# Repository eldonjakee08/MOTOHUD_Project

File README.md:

# MotoHUD Project
A proof of concept project that aims to integrate a heads-up display (HUD) into a motorcycle helmet, projecting real-time ECU sensor data such as speed, RPM, and engine load directly into the rider’s field of view.

This project aims to enhance riders situational awareness and safety by delivering vehicle metrics without requiring the rider to look away from the road.

# System Architecture & Overview

<br>**TRANSMITTER**
1. STM32WB5MMG MCU wakes up every 100ms to poll the motorcycle CAN bus for ECU sensor data.(e.g. Speed, RPM, Engine Load, etc.) 
2. Transmitter sends the ECU sensor data via BLE.
3. MCU goes into deep sleep state to conserve power. 

<br>**RECEIVER**
1. STM32WB5MMG MCU wakes up from deep sleep upon reception of sensor data from transmitter
2. MCU Parses the received data and displays into OLED screen.
3. Beamsplitter glass reflects the projection from OLED screen into the riders field of view
4. MCU returns into deep sleep state to conserve power.

# Project Milestones & Progress
1. Designed and fabricated a custom development board for STM32WB5MMG MCU.
2. Designed and fabricated custom module for LM3671 to power the receiver.
3. Designed the initial hardware for both Receiver and Transmitter.
4. Developed custom driver for SSD1315 OLED driver.
5. On-going development of custom driver for MCP2515 CAN controller

# Pending Tasks
1. Develop application firmware for both receiver and transmitter.
2. Fabricate the hardware for both receiver and transmitter.
3. Design and fabricate a receiver enclosure for optimal mounting into the helmet.
4. Design and fabricate an enclosure for the transmitter.

 # Future Improvements & Optimizations
 1. Optimize I2C and SPI data transmission using Direct Memory Access (DMA) to achieve higher throughput and lower power consumption.
 2. Design a load sharing protection circuit for the receiver’s battery to support simultaneous operation and charging.
 3. Music streaming feature via Bluetooth Low Energy (BLE).
 4. END VISION: Seamlessly stream live ECU sensor data into the helmets visor, delivering a real-time Augmented Reality (AR) experience.

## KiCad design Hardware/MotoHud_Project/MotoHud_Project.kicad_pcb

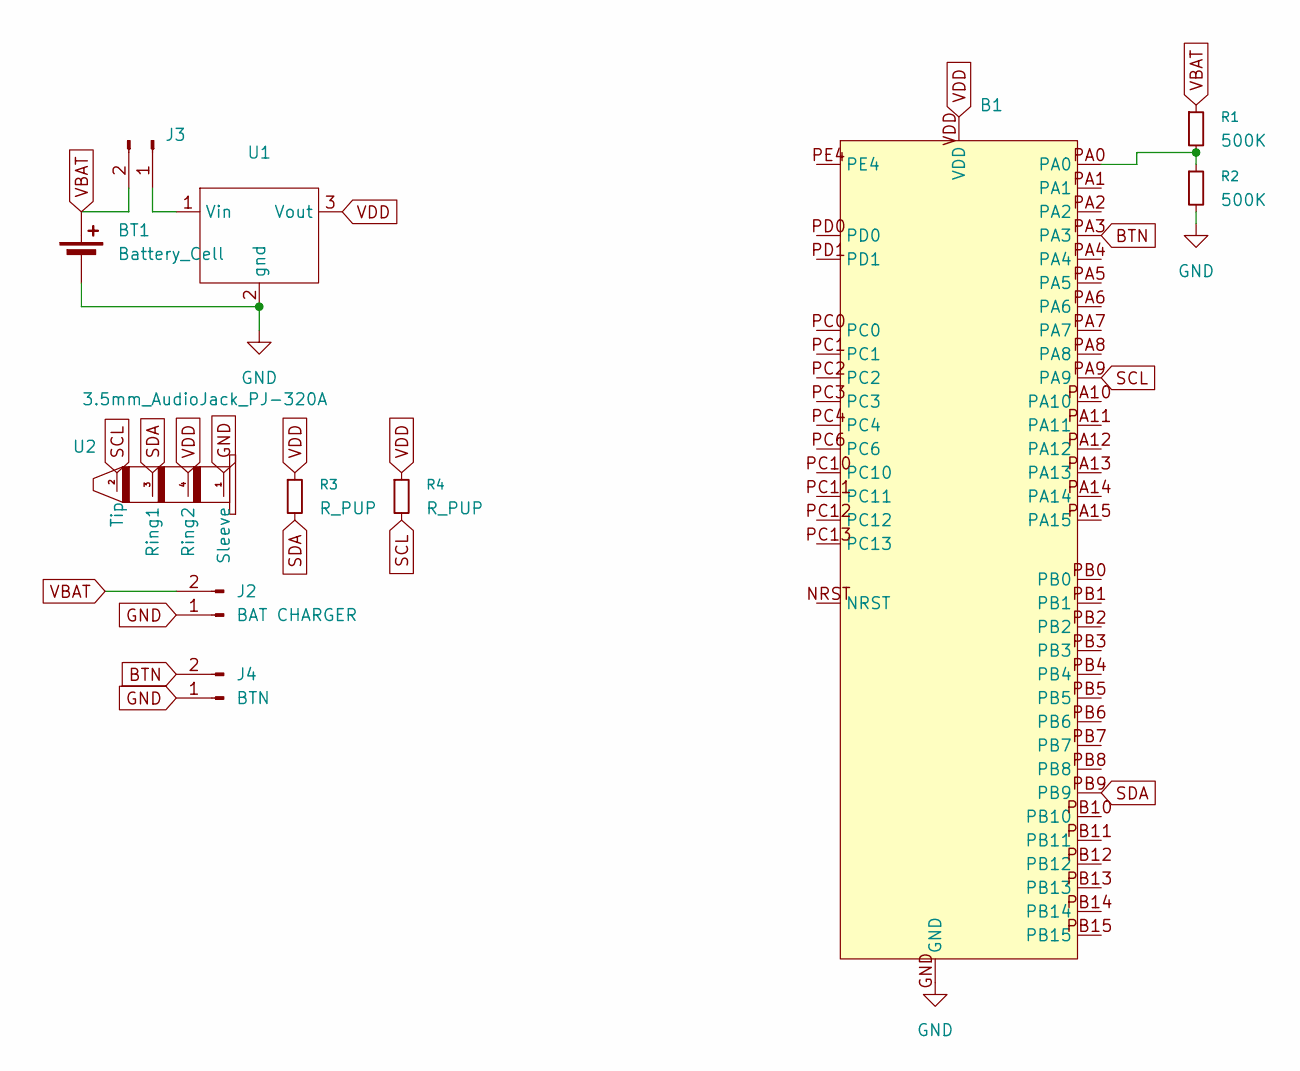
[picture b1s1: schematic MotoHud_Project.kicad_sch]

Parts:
B1: STM32WB5MMG_CUSTOM_DEVBOARD
BT1: Battery_Cell; PinHeader_1x02_P2.54mm_Vertical
J2: BAT CHARGER; PinHeader_1x02_P2.54mm_Vertical
J3: Conn_01x02_Pin; PinHeader_1x02_P2.54mm_Vertical
J4: BTN; PinHeader_1x02_P2.54mm_Vertical
R1, R2: 500K; R_0603_1608Metric_Pad0.98x0.95mm_HandSolder
R3, R4: R_PUP; R_Axial_DIN0207_L6.3mm_D2.5mm_P10.16mm_Horizontal
U1: LM3671_MODULE
U2: 3.5mm_AudioJack_PJ-320A; 3.5mm_AudioJack_PJ-320A_NoGuide

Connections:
BTN: B1.PA3, J4.2
GND: B1.GND, BT1.2 (-), J2.1, J4.1, R2.2, U1.2 (gnd), U2.1 (Sleeve)
unnamed: B1.PA0, R1.2, R2.1
unnamed: J3.1, U1.1 (Vin)
SCL: B1.PA9, R4.2, U2.2 (Tip)
SDA: B1.PB9, R3.2, U2.3 (Ring1)
VBAT: BT1.1 (+), J2.2, J3.2, R1.1
VDD: B1.VDD, R3.1, R4.1, U1.3 (Vout), U2.4 (Ring2)

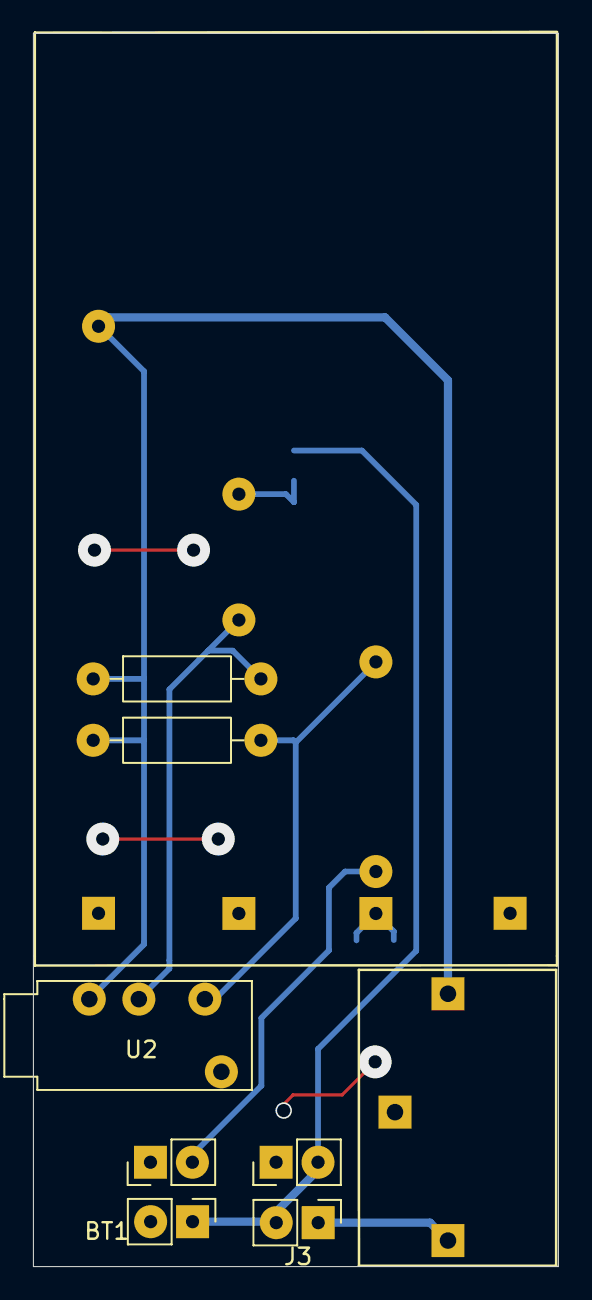
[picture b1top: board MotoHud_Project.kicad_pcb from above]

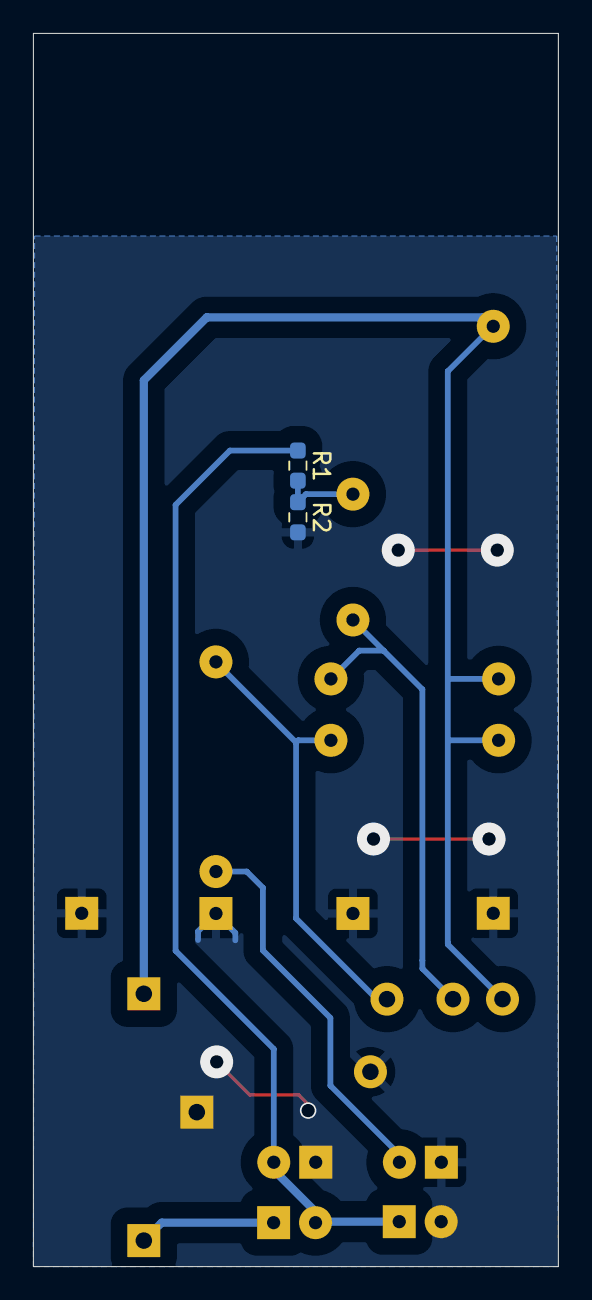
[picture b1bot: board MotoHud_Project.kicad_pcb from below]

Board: 2 copper layers, 31.8 x 74.7 mm, 11 parts (2 on the bottom side), 8 nets.

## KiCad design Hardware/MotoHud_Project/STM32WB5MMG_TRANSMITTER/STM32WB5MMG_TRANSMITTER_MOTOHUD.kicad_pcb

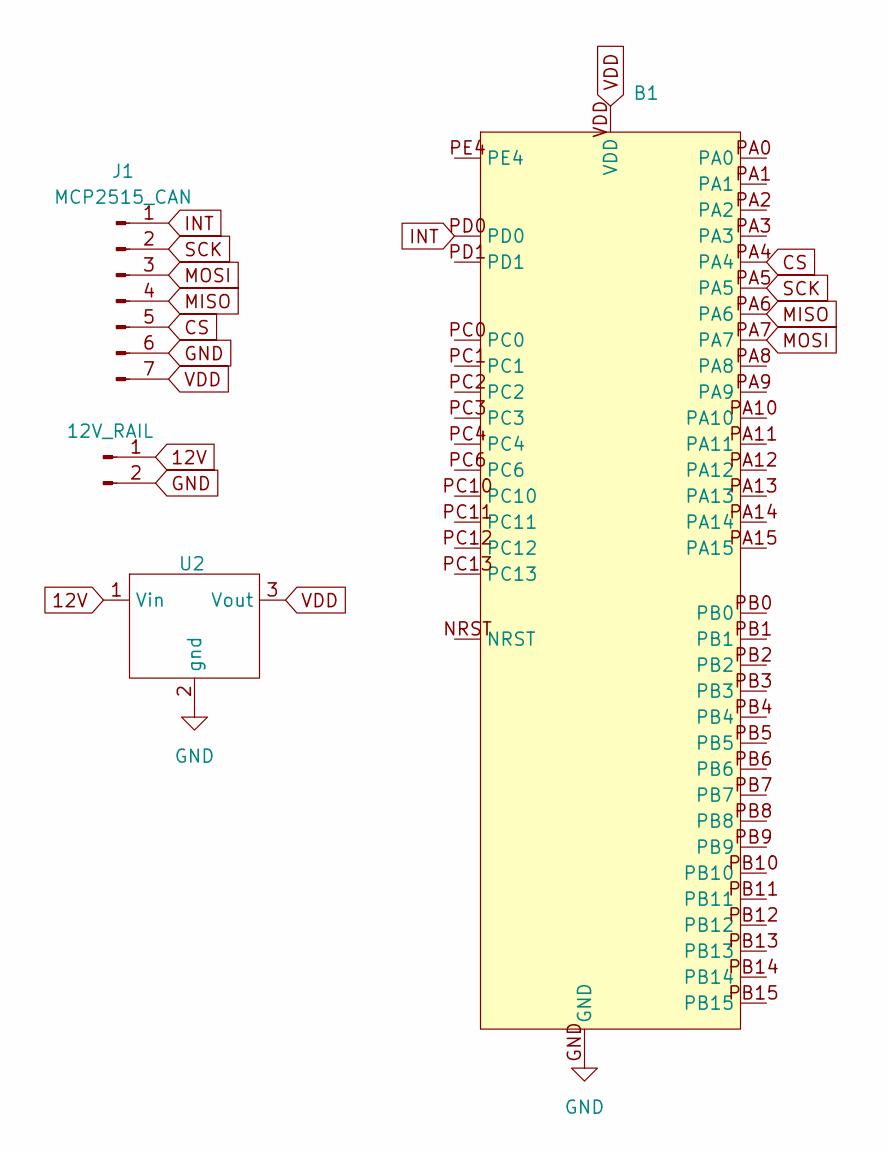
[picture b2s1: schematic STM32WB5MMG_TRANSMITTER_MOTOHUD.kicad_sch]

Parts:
B1: STM32WB5MMG_CUSTOM_DEVBOARD
J1: MCP2515_CAN; MCP2515_MODULE
J3: 12V_RAIL; PinHeader_1x02_P2.54mm_Vertical
U2: MP1584EN_DCtoDC_REGULATOR

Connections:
12V: J3.1, U2.1 (Vin)
CS: B1.PA4, J1.5
GND: B1.GND, J1.6, J3.2, U2.2 (gnd)
INT: B1.PD0, J1.1
MISO: B1.PA6, J1.4
MOSI: B1.PA7, J1.3
SCK: B1.PA5, J1.2
VDD: B1.VDD, J1.7, U2.3 (Vout)

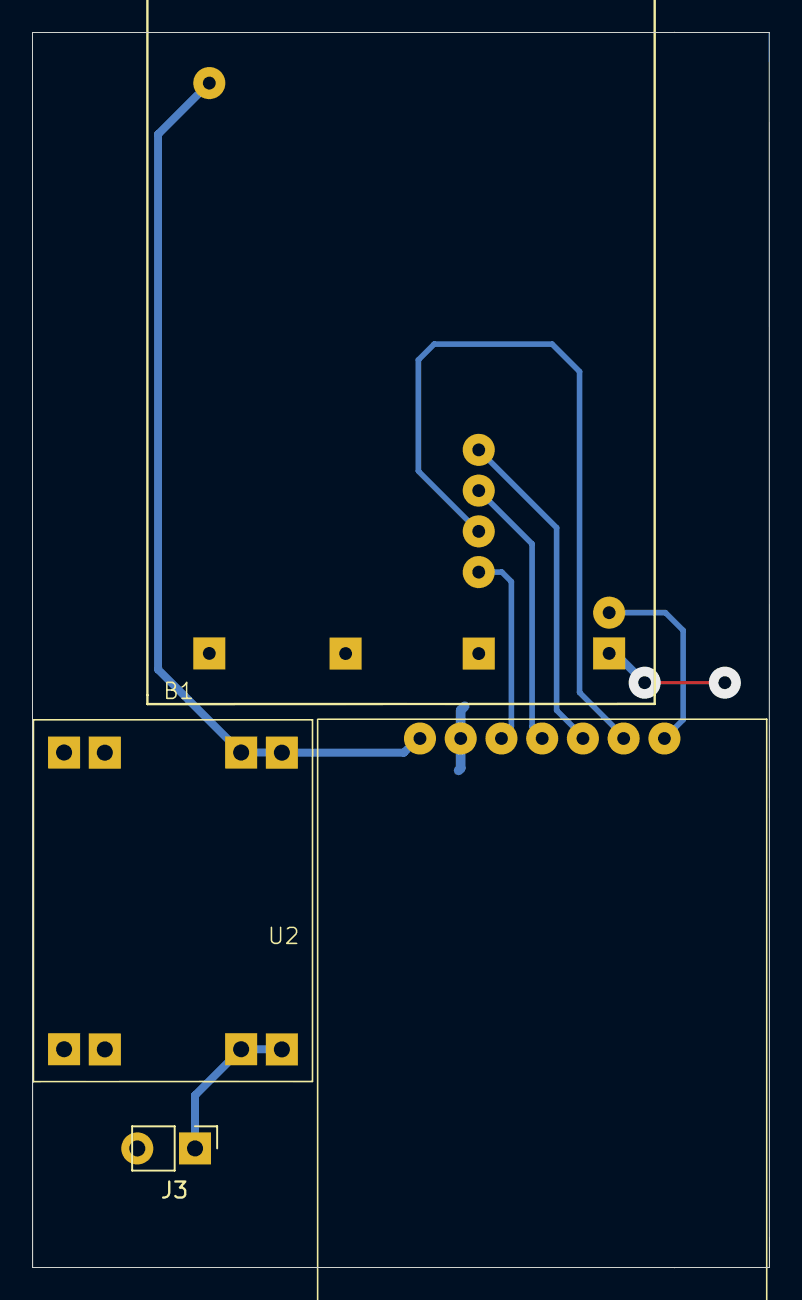
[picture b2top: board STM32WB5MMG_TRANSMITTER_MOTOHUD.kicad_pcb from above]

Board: 2 copper layers, 46.0 x 77.0 mm, 4 parts (0 on the bottom side), 8 nets.

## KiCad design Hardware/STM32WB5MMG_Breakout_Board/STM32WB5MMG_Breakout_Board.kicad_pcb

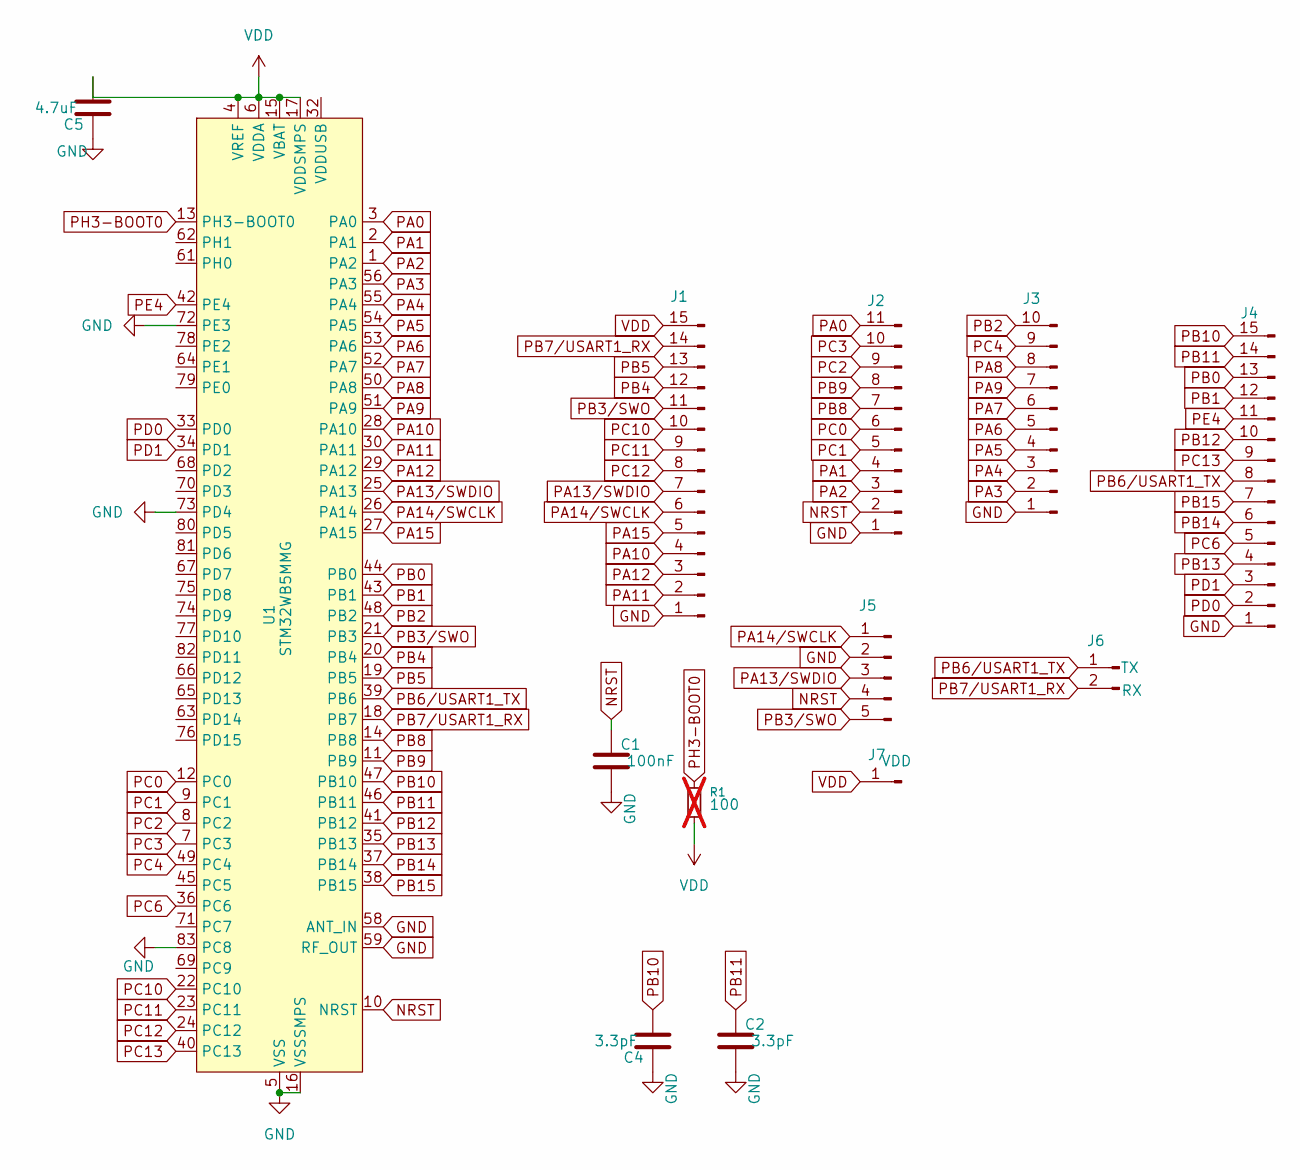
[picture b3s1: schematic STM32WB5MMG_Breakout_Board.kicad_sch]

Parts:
C1: 100nF; C_0603_1608Metric
C2, C4: 3.3pF; C_0201_0603Metric
C5: 4.7uF; C_0603_1608Metric
J1, J4: PinHeader_1x15_P2.54mm_Vertical
J2: Conn_01x11_Pin; PinHeader_1x11_P2.54mm_Vertical
J3: PinHeader_1x10_P2.54mm_Vertical
J5: PinHeader_1x05_P2.54mm_Vertical
J6: PinHeader_1x02_P2.54mm_Vertical
J7: VDD; PinHeader_1x01_P2.54mm_Vertical
R1: 100; R_0201_0603Metric; not fitted
U1: STM32WB5MMG; ST-SiP-LGA-86-11x7.3mm

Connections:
GND: C1.2, C2.2, C4.1, C5.1, J1.1, J2.1, J3.1, J4.1, J5.2, U1.5 (VSS), U1.16 (VSSSMPS), U1.31 (VSS), U1.57 (VSS), U1.58 (ANT_IN), U1.59 (RF_OUT), U1.60 (VSS), U1.72 (PE3), U1.73 (PD4), U1.83 (PC8), U1.84 (VSS), U1.86 (VSS)
NRST: C1.1, J2.2, J5.4, U1.10 (NRST)
PA0: J2.11, U1.3 (PA0)
PA1: J2.4, U1.2 (PA1)
PA2: J2.3, U1.1 (PA2)
PA3: J3.2, U1.56 (PA3)
PA4: J3.3, U1.55 (PA4)
PA5: J3.4, U1.54 (PA5)
PA6: J3.5, U1.53 (PA6)
PA7: J3.6, U1.52 (PA7)
PA8: J3.8, U1.50 (PA8)
PA9: J3.7, U1.51 (PA9)
PA10: J1.4, U1.28 (PA10)
PA11: J1.2, U1.30 (PA11)
PA12: J1.3, U1.29 (PA12)
PA13/SWDIO: J1.7, J5.3, U1.25 (PA13)
PA14/SWCLK: J1.6, J5.1, U1.26 (PA14)
PA15: J1.5, U1.27 (PA15)
PB0: J4.13, U1.44 (PB0)
PB1: J4.12, U1.43 (PB1)
PB2: J3.10, U1.48 (PB2)
PB3/SWO: J1.11, J5.5, U1.21 (PB3)
PB4: J1.12, U1.20 (PB4)
PB5: J1.13, U1.19 (PB5)
PB6/USART1_TX: J4.8, J6.1, U1.39 (PB6)
PB7/USART1_RX: J1.14, J6.2, U1.18 (PB7)
PB8: J2.7, U1.14 (PB8)
PB9: J2.8, U1.11 (PB9)
PB10: C4.2, J4.15, U1.47 (PB10)
PB11: C2.1, J4.14, U1.46 (PB11)
PB12: J4.10, U1.41 (PB12)
PB13: J4.4, U1.35 (PB13)
PB14: J4.6, U1.37 (PB14)
PB15: J4.7, U1.38 (PB15)
PC0: J2.6, U1.12 (PC0)
PC1: J2.5, U1.9 (PC1)
PC2: J2.9, U1.8 (PC2)
PC3: J2.10, U1.7 (PC3)
PC4: J3.9, U1.49 (PC4)
PC6: J4.5, U1.36 (PC6)
PC10: J1.10, U1.22 (PC10)
PC11: J1.9, U1.23 (PC11)
PC12: J1.8, U1.24 (PC12)
PC13: J4.9, U1.40 (PC13)
PD0: J4.2, U1.33 (PD0)
PD1: J4.3, U1.34 (PD1)
PE4: J4.11, U1.42 (PE4)
PH3-BOOT0: R1.1, U1.13 (PH3-BOOT0)
VDD: C5.2, J1.15, J7.1, R1.2, U1.4 (VREF), U1.6 (VDDA), U1.15 (VBAT), U1.17 (VDDSMPS)

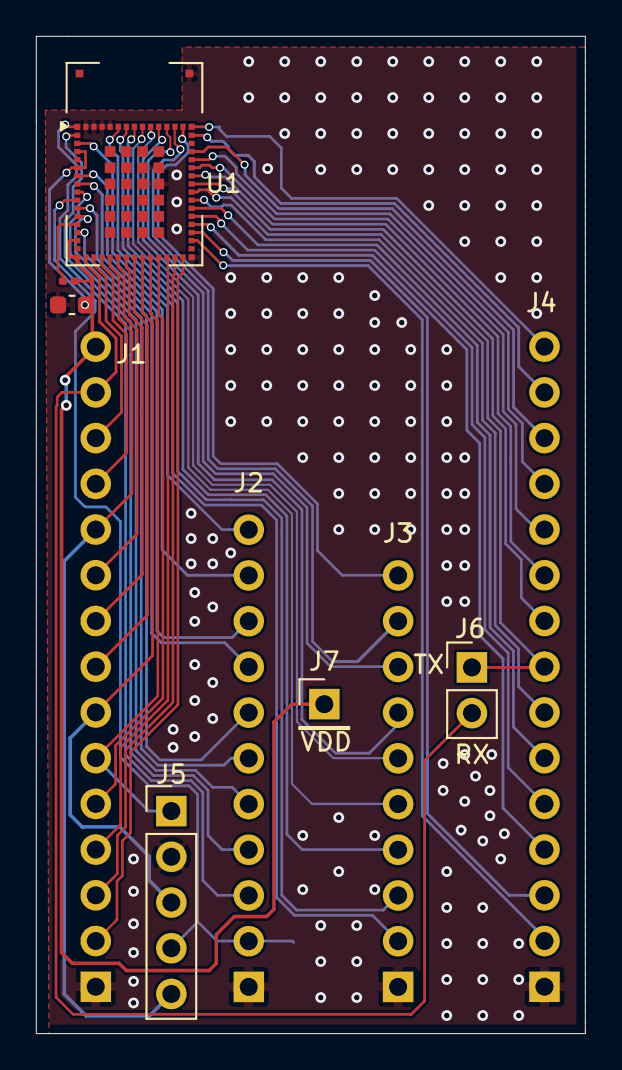
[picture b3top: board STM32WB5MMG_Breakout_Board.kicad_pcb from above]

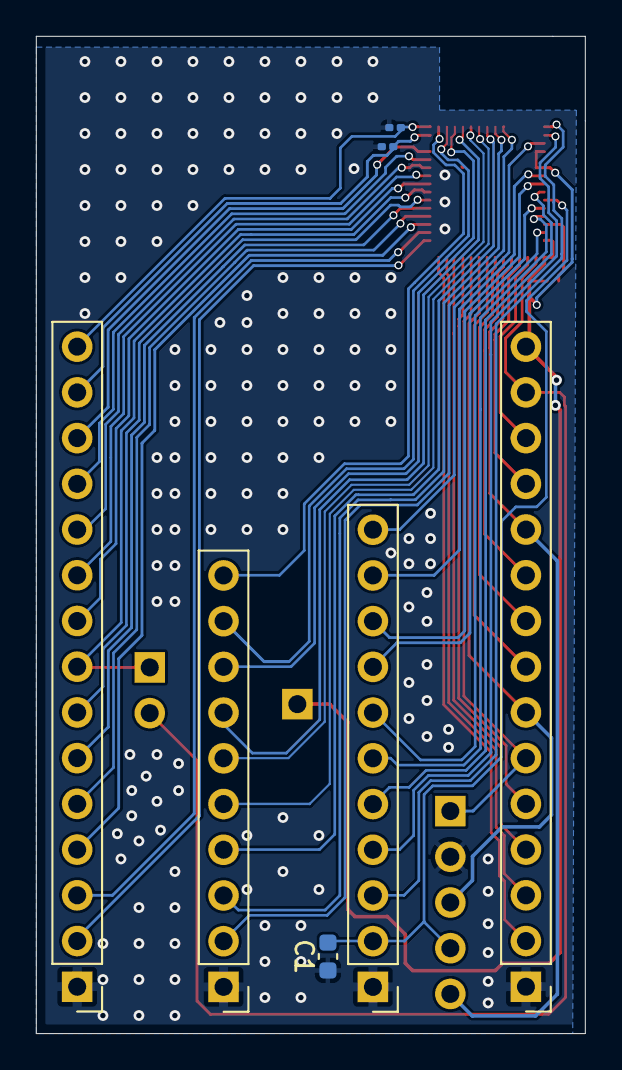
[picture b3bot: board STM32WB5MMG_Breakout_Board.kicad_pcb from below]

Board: 2 copper layers, 30.5 x 55.4 mm, 13 parts (7 on the bottom side), 49 nets.

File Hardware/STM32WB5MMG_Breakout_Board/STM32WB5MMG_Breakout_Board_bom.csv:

Comment,Designator,Footprint
100nF,C1,Capacitor_SMD:C_0603_1608Metric
3.3pF,"C2,C4",Capacitor_SMD:C_0201_0603Metric
4.7uF,C5,Capacitor_SMD:C_0603_1608Metric
Conn_01x15_Pin,"J1,J4",Connector_PinHeader_2.54mm:PinHeader_1x15_P2.54mm_Vertical
Conn_01x11_Pin,J2,Connector_PinHeader_2.54mm:PinHeader_1x11_P2.54mm_Vertical
Conn_01x10_Pin,J3,Connector_PinHeader_2.54mm:PinHeader_1x10_P2.54mm_Vertical
Conn_01x05_Pin,J5,Connector_PinHeader_2.54mm:PinHeader_1x05_P2.54mm_Vertical
Conn_01x2_Pin,J6,Connector_PinHeader_2.54mm:PinHeader_1x02_P2.54mm_Vertical
Conn_01x1_Pin,J7,Connector_PinHeader_2.54mm:PinHeader_1x01_P2.54mm_Vertical
100 Ohms,R1,Resistor_SMD:R_0201_0603Metric
STM32WB5MMG,U1,RF_Module:ST-SiP-LGA-86-11x7.3mm

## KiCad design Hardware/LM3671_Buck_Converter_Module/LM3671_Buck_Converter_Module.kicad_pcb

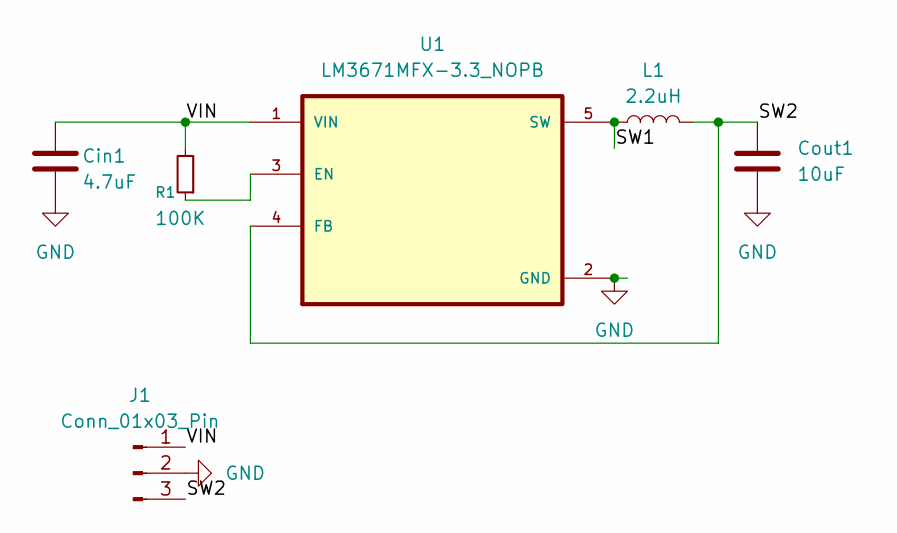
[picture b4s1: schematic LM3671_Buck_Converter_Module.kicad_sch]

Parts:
Cin1: 4.7uF; C_1206_3216Metric_Pad1.33x1.80mm_HandSolder
Cout1: 10uF; C_1206_3216Metric_Pad1.33x1.80mm_HandSolder
J1: Conn_01x03_Pin; PinHeader_1x03_P2.54mm_Vertical
L1: 2.2uH; 0806(2016 METRIC)_CIGT201610_SAM
R1: 100K; R_0603_1608Metric_Pad0.98x0.95mm_HandSolder
U1: LM3671MFX-3.3_NOPB; LM3671MFX-3.3_NOPB_SOT95P280X145-5N

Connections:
/SW1: L1.1, U1.5 (SW)
/SW2: Cout1.1, J1.3, L1.2, U1.4 (FB)
/VIN: Cin1.1, J1.1, R1.2, U1.1 (VIN)
GND: Cin1.2, Cout1.2, J1.2, U1.2 (GND)
unnamed: R1.1, U1.3 (EN)

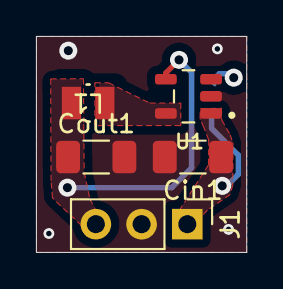
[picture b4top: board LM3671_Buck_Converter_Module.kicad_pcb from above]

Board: 2 copper layers, 11.7 x 12.0 mm, 6 parts (1 on the bottom side), 5 nets.

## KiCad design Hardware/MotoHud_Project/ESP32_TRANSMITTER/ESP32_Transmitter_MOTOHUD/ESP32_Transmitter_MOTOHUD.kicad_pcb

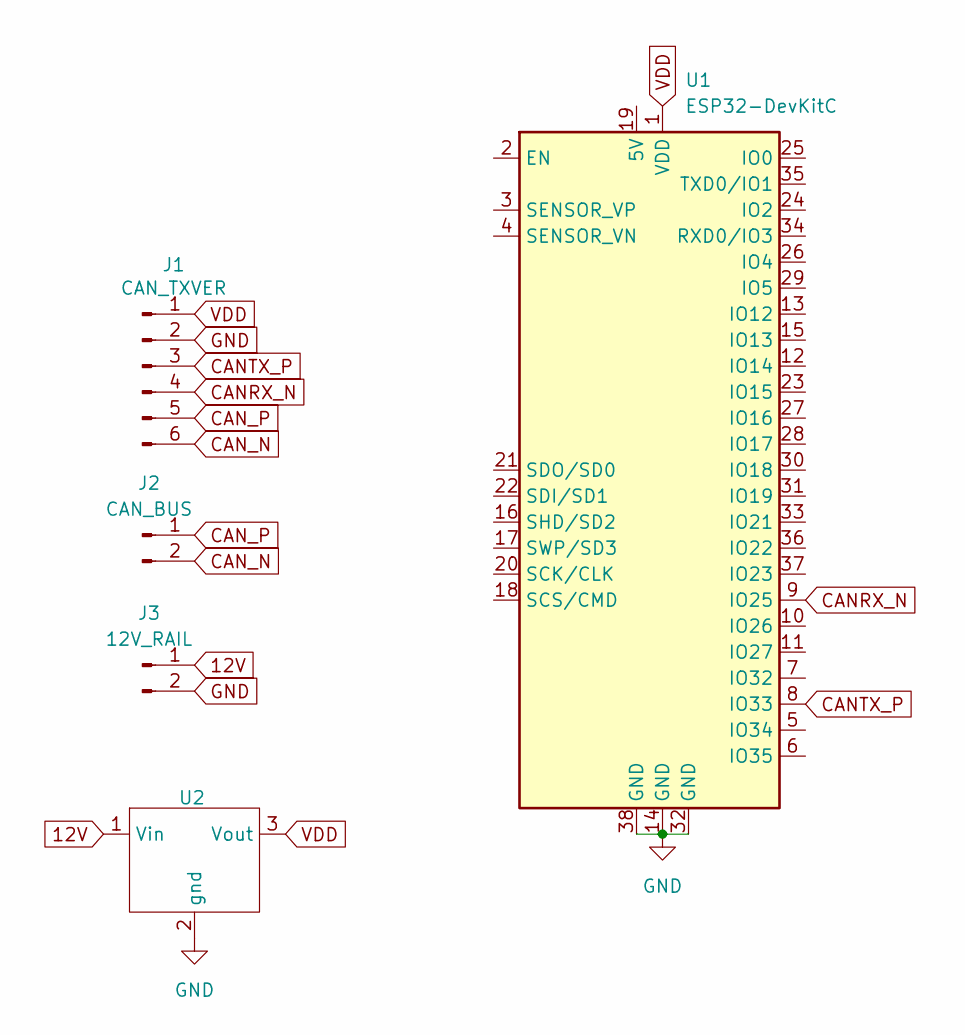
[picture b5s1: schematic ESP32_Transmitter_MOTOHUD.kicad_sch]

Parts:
J1: CAN_TXVER; PinHeader_1x06_P2.54mm_Vertical
J2: CAN_BUS; PinHeader_1x02_P2.54mm_Vertical
J3: 12V_RAIL; PinHeader_1x02_P2.54mm_Vertical
U1: ESP32-DevKitC
U2: MP1584EN_DCtoDC_REGULATOR

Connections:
12V: J3.1, U2.1 (Vin)
CANRX_N: J1.4, U1.9 (IO25)
CANTX_P: J1.3, U1.8 (IO33)
CAN_N: J1.6, J2.2
CAN_P: J1.5, J2.1
GND: J1.2, J3.2, U1.14 (GND), U1.32 (GND), U1.38 (GND), U2.2 (gnd)
VDD: J1.1, U1.1 (VDD), U2.3 (Vout)

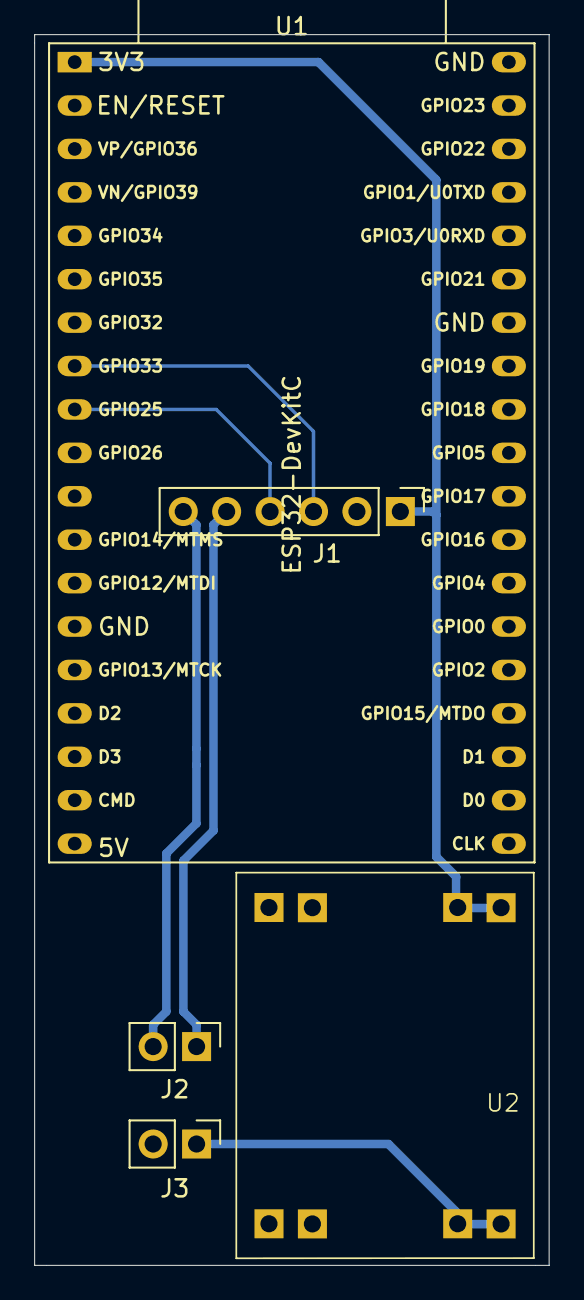
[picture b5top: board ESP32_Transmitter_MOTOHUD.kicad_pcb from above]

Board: 2 copper layers, 30.1 x 72.0 mm, 5 parts (0 on the bottom side), 7 nets.

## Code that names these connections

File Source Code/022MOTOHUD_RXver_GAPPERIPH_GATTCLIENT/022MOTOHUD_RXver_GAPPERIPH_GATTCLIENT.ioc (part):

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Mcu.Name=STM32WB5MMGHx
Mcu.Package=LGA86
Mcu.UserName=STM32WB5MMGHx
PA0.Signal=ADCx_IN5
PA3.GPIOParameters=GPIO_PuPd,GPIO_Label
PA3.GPIO_Label=USR_BTN1
PA3.GPIO_PuPd=GPIO_PULLUP
PA3.Signal=GPIO_Input
PA9.Mode=I2C
PA9.Signal=I2C1_SCL
PB6.Mode=Asynchronous
PB6.Signal=USART1_TX
PB7.Mode=Asynchronous
PB7.Signal=USART1_RX
PB9.Mode=I2C
PB9.Signal=I2C1_SDA
PC2.GPIOParameters=GPIO_Speed,PinState,GPIO_PuPd
PC2.GPIO_PuPd=GPIO_NOPULL
PC2.GPIO_Speed=GPIO_SPEED_FREQ_VERY_HIGH
PC2.PinState=GPIO_PIN_RESET
PC2.Signal=GPIO_Output
RCC.HSE_VALUE=32000000
RCC.SYSCLKFreq_VALUE=64000000
RCC.SYSCLKSource=RCC_SYSCLKSOURCE_PLLCLK
board=custom

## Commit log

2025-09-05 added project files
2025-09-08 updated rxver and txver hardware
2025-09-10 updated stm32wb5mmg breakout board hardware
2025-09-15 updated project source files
2025-09-18 updated hardware
2025-09-20 updated source files
